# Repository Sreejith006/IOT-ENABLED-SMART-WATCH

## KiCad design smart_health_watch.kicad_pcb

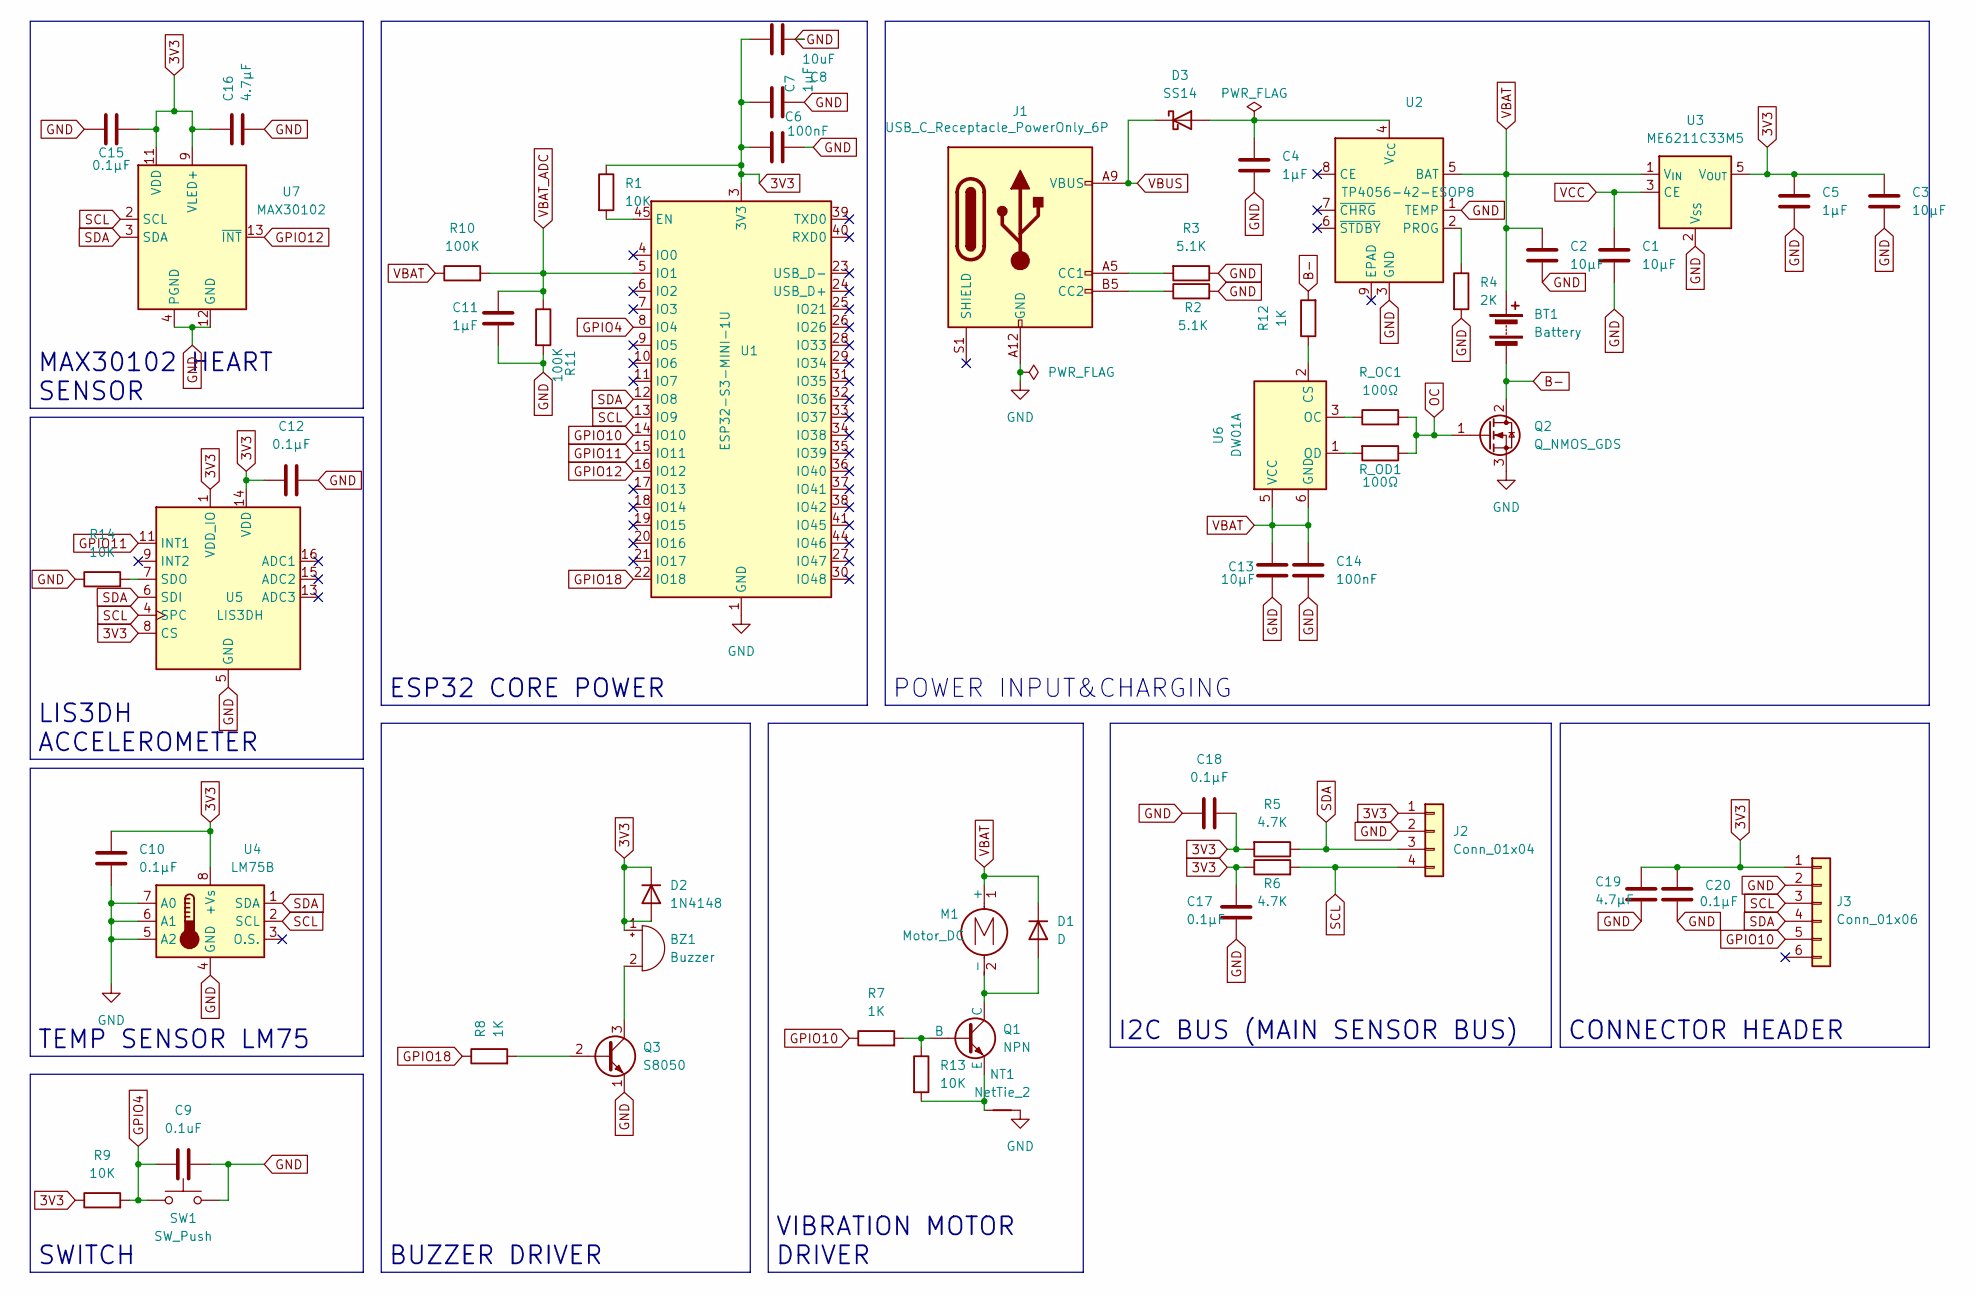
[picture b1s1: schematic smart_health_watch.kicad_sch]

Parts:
BT1: Battery; JST_PH_B2B-PH-K_1x02_P2.00mm_Vertical
BZ1: Buzzer; MagneticBuzzer_PUI_SMT-1028-T-2-R
C1, C2, C3, C13: 10µF; C_0603_1608Metric
C4, C5, C7, C11: 1µF; C_0603_1608Metric
C6, C14: 100nF; C_0603_1608Metric
C8: 10uF; C_0603_1608Metric
C9: 0.1uF; C_0603_1608Metric
C10, C12, C15, C17, C18, C20: 0.1µF; C_0603_1608Metric
C16, C19: 4.7µF; C_0603_1608Metric
D1: D; D_SOD-123
D2: 1N4148; D_SOD-123
D3: SS14; D_SMA
J1: USB_C_Receptacle_PowerOnly_6P; USB_C_Receptacle_HRO_TYPE-C-31-M-12
J2: Conn_01x04; PinHeader_1x04_P2.54mm_Vertical
J3: Conn_01x06; PinHeader_1x06_P2.54mm_Vertical
M1: Motor_DC; SolderWire-0.5sqmm_1x02_P4.6mm_D0.9mm_OD2.1mm
NT1: NetTie_2; NetTie-2_SMD_Pad0.5mm
Q1: NPN; SOT-23
Q2: Q_NMOS_GDS; TSOT-23
Q3: S8050; SOT-23
R1, R9, R13, R14: 10K; R_0603_1608Metric
R2, R3: 5.1K; R_0603_1608Metric
R4: 2K; R_0603_1608Metric
R5, R6: 4.7K; R_0603_1608Metric
R7, R8, R12: 1K; R_0603_1608Metric
R10, R11: 100K; R_0603_1608Metric
R_OC1: 100Ω; R_0603_1608Metric
R_OD1: 100Ω; R_0603_1608Metric
SW1: SW_Push; SW_SPST_TL3342
U1: ESP32-S3-MINI-1U; ESP32-S2-MINI-1U
U2: TP4056-42-ESOP8; SOIC-8-1EP_3.9x4.9mm_P1.27mm_EP2.41x3.3mm_ThermalVias
U3: ME6211C33M5; SOT-23-5
U4: LM75B; SOIC-8_3.9x4.9mm_P1.27mm
U5: LIS3DH; LGA-16_3x3mm_P0.5mm_LayoutBorder3x5y
U6: DW01A; SOT-23-6
U7: MAX30102; Maxim_OLGA-14_3.3x5.6mm_P0.8mm

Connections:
3V3: BZ1.1 (+), C3.1, C5.1, C6.2, C7.1, C8.2, C10.2, C12.1, C15.1, C16.1, C17.1, C18.1, C19.1, C20.1, D2.1 (K), D2.2 (A), J2.1, J3.1, R1.1, R5.2, R6.1, R9.1, U1.3 (3V3), U3.5 (V_{OUT}), U4.8 (+Vs), U5.1 (VDD_IO), U5.8 (CS), U5.14 (VDD), U7.9 (VLED+), U7.10 (VLED+), U7.11 (VDD)
B-: BT1.2 (-), Q2.2 (D), R12.2
GND: C1.2, C2.1, C3.2, C4.2, C5.2, C6.1, C7.2, C8.1, C9.2, C10.1, C11.1, C12.2, C13.2, C14.2, C15.2, C16.2, C17.2, C18.2, C19.2, C20.2, J1.A1, J1.A12 (GND), J1.B1, J1.B12 (GND), J2.2, J3.2, NT1.1, Q2.3 (S), Q3.1 (E), R2.2, R3.1, R4.2, R11.2, R14.1, SW1.2, U1.1 (GND), U1.2 (GND), U1.42 (GND), U1.43 (GND), U1.46 (GND), U1.47 (GND), U1.48 (GND), U1.49 (GND), U1.50 (GND), U1.51 (GND), U1.52 (GND), U1.53 (GND), U1.54 (GND), U1.55 (GND), U1.56 (GND), U1.57 (GND), U1.58 (GND), U1.59 (GND), U1.60 (GND), U1.61 (GND), U1.62 (GND), U1.63 (GND), U1.64 (GND), U1.65 (GND), U2.1 (TEMP), U2.3 (GND), U3.2 (V_{SS}), U4.4 (GND), U4.5 (A2), U4.6 (A1), U4.7 (A0), U5.5 (GND), U5.10 (GND), U5.12 (GND), U7.4 (PGND), U7.12 (GND)
GPIO4: C9.1, R9.2, SW1.1, U1.8 (IO4)
GPIO10: J3.5, R7.1, U1.14 (IO10)
GPIO11: U1.15 (IO11), U5.11 (INT1)
GPIO12: U1.16 (IO12), U7.13 (~INT)
GPIO18: R8.1, U1.22 (IO18)
unnamed: BZ1.2 (-), Q3.3 (C)
unnamed: D1.2 (A), M1.2 (-), Q1.1 (C)
unnamed: C4.1, D3.2 (A), U2.4 (V_{CC})
unnamed: J1.A5 (CC1), R3.2
unnamed: J1.B5 (CC2), R2.1
unnamed: Q1.2 (B), R7.2, R13.1
unnamed: NT1.2, Q1.3 (E), R13.2
unnamed: Q3.2 (B), R8.2
unnamed: R1.2, U1.45 (EN)
unnamed: R4.1, U2.2 (PROG)
unnamed: R14.2, U5.7 (SDO)
unnamed: R12.1, U6.2 (CS)
unnamed: R_OC1.1, U6.3 (OC)
unnamed: R_OD1.2, U6.1 (OD)
OC: Q2.1 (G), R_OC1.2, R_OD1.1
SCL: J2.4, J3.3, R6.2, U1.13 (IO9), U4.2 (SCL), U5.4 (SPC), U7.2 (SCL)
SDA: J2.3, J3.4, R5.1, U1.12 (IO8), U4.1 (SDA), U5.6 (SDI), U7.3 (SDA)
VBAT: BT1.1 (+), C2.2, C13.1, C14.1, D1.1 (K), M1.1 (+), R10.1, U2.5 (BAT), U3.1 (V_{IN}), U6.5 (VCC), U6.6 (GND)
VBAT_ADC: C11.2, R10.2, R11.1, U1.5 (IO1)
VBUS: D3.1 (K), J1.A4, J1.A9 (VBUS), J1.B4, J1.B9 (VBUS)
VCC: C1.1, U3.3 (CE)

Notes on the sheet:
POWER INPUT&CHARGING
MAX30102 HEART SENSOR
BUZZER DRIVER
SWITCH
I2C BUS (MAIN SENSOR BUS)
TEMP SENSOR LM75
LIS3DH ACCELEROMETER
CONNECTOR HEADER
VIBRATION MOTOR DRIVER
ESP32 CORE POWER

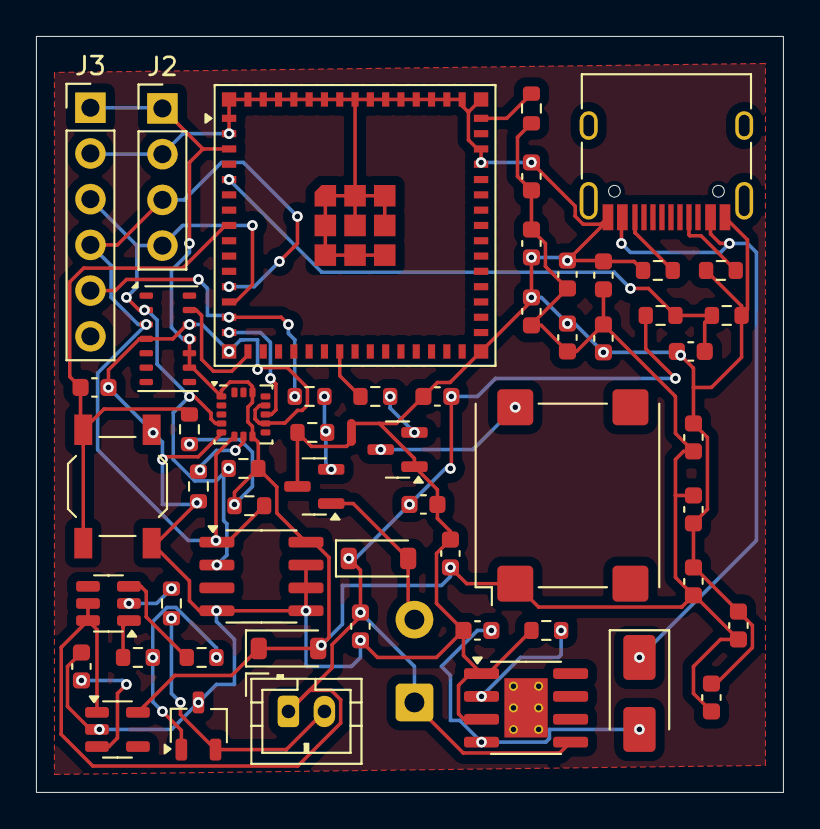
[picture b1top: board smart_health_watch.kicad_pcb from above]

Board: 2 copper layers, 41.5 x 42.0 mm, 57 parts (0 on the bottom side), 29 nets.

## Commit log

2026-02-27 PRODUCT
2026-02-27 Add files via upload
    DESIGN COMPLETED
